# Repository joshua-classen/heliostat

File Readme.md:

Sun Follower | heliostat

This repo contains code for my heliostat robot which is able to align itself to a light source.

The heliostat in action can be viewed on youtube:

I developed and built the heliostat in year 2015
Years ago I uploaded the files to bitbucket: https://bitbucket.org/ckrex/myheliostatcontrol/src/master/

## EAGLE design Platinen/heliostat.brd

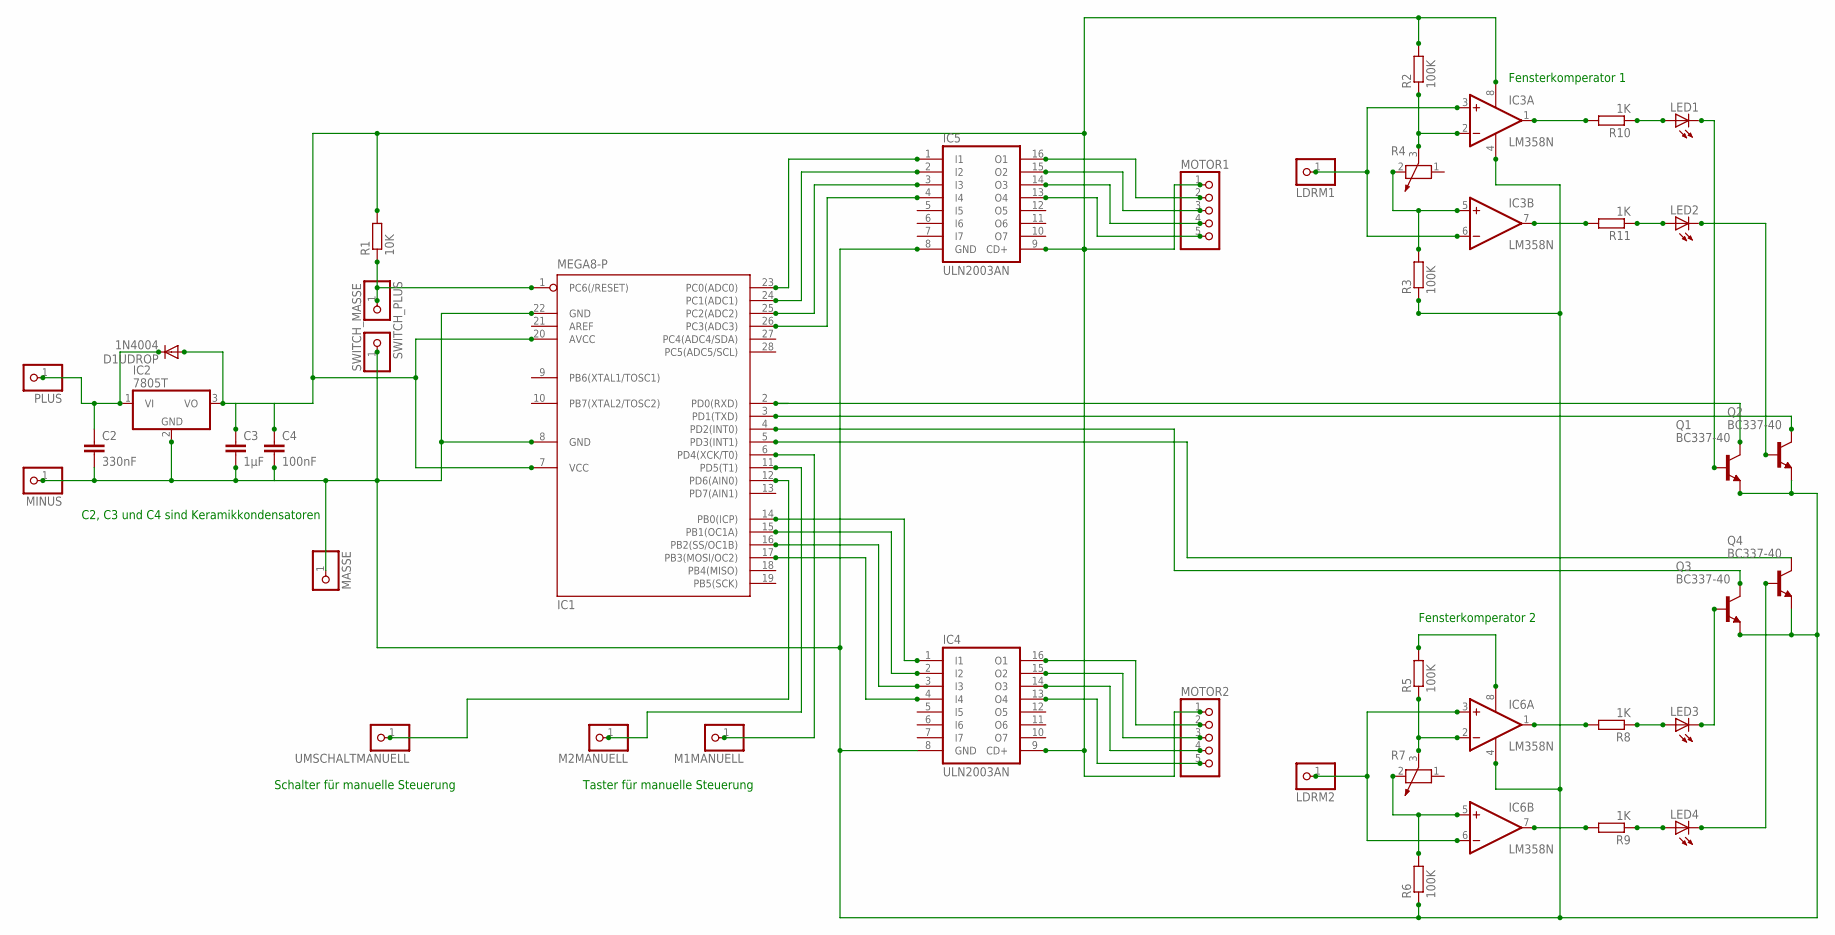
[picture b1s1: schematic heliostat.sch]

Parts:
C2: 330nF; C025-024X044
C3: 1µF; C025-024X044
C4: 100nF; C025-024X044
D1UDROP: 1N4004; DO41-10
IC1: MEGA8-P; DIL28-3
IC2: 7805T; TO220H
IC3, IC6: LM358N; DIL08
IC4, IC5: ULN2003AN; DIL16
LDRM1, LDRM2: PINHD-1X1; 1X01
LED1, LED2, LED3, LED4: LED_ELD260; LED_LD260
M1MANUELL, M2MANUELL: PINHD-1X1; 1X01
MASSE: PINHD-1X1; 1X01
MINUS: PINHD-1X1; 1X01
MOTOR1, MOTOR2: PINHD-1X5; 1X05
PLUS: PINHD-1X1; 1X01
Q1, Q2, Q3, Q4: BC337-40; TO92
R1: 10K; 0204V
R2, R3, R5, R6: 100K; 0204V
R4, R7: POTENTIOMETER_PT-10; PT-10
R8, R9, R10, R11: 1K; 0204V
SWITCH_MASSE: PINHD-1X1; 1X01
SWITCH_PLUS: PINHD-1X1; 1X01
UMSCHALTMANUELL: PINHD-1X1; 1X01

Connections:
unnamed: IC1.23 (PC0(ADC0)), IC5.1 (I1)
unnamed: IC3.2 (-IN), R2.1, R4.3
unnamed: IC1.24 (PC1(ADC1)), IC5.2 (I2)
unnamed: C2.1, D1UDROP.C, IC2.1 (VI), PLUS.1
unnamed: IC1.2 (PD0(RXD)), Q1.3 (C)
unnamed: IC1.25 (PC2(ADC2)), IC5.3 (I3)
unnamed: IC1.26 (PC3(ADC3)), IC5.4 (I4)
unnamed: IC5.16 (O1), MOTOR1.2
unnamed: IC5.15 (O2), MOTOR1.3
unnamed: IC5.14 (O3), MOTOR1.4
unnamed: IC5.13 (O4), MOTOR1.5
unnamed: IC1.14 (PB0(ICP)), IC4.1 (I1)
unnamed: IC1.15 (PB1(OC1A)), IC4.2 (I2)
unnamed: IC1.16 (PB2(SS/OC1B)), IC4.3 (I3)
unnamed: IC1.17 (PB3(MOSI/OC2)), IC4.4 (I4)
unnamed: IC4.16 (O1), MOTOR2.2
unnamed: IC4.15 (O2), MOTOR2.3
unnamed: IC4.14 (O3), MOTOR2.4
unnamed: IC4.13 (O4), MOTOR2.5
unnamed: C3.1, C4.1, D1UDROP.A, IC1.7 (VCC), IC1.20 (AVCC), IC2.3 (VO), IC3.8 (V+), IC4.9 (CD+), IC5.9 (CD+), MOTOR1.1, MOTOR2.1, R1.2, R2.2
unnamed: IC3.5 (+IN), R3.2, R4.2
unnamed: IC6.8 (V+), R5.2
unnamed: IC3.3 (+IN), IC3.6 (-IN), LDRM1.1
unnamed: IC6.1 (OUT), R8.2
unnamed: IC6.2 (-IN), R5.1, R7.3
unnamed: IC6.5 (+IN), R6.2, R7.2
unnamed: IC6.3 (+IN), IC6.6 (-IN), LDRM2.1
unnamed: LED3.A, R8.1
unnamed: IC6.7 (OUT), R9.2
unnamed: LED4.A, R9.1
unnamed: IC3.7 (OUT), R11.2
unnamed: LED2.A, R11.1
unnamed: IC3.1 (OUT), R10.2
unnamed: LED1.A, R10.1
unnamed: IC1.1 (PC6(/RESET)), R1.1, SWITCH_PLUS.1
unnamed: IC1.6 (PD4(XCK/T0)), M1MANUELL.1
unnamed: LED1.K (C), Q1.2 (B)
unnamed: LED2.K (C), Q2.2 (B)
unnamed: IC1.3 (PD1(TXD)), Q2.3 (C)
unnamed: LED3.K (C), Q3.2 (B)
unnamed: IC1.4 (PD2(INT0)), Q3.3 (C)
unnamed: LED4.K (C), Q4.2 (B)
unnamed: IC1.5 (PD3(INT1)), Q4.3 (C)
unnamed: IC1.11 (PD5(T1)), M2MANUELL.1
unnamed: C2.2, C3.2, C4.2, IC1.8 (GND), IC1.22 (GND), IC2.2 (GND), IC3.4 (V-), IC4.8 (GND), IC5.8 (GND), IC6.4 (V-), MASSE.1, MINUS.1, Q1.1 (E), Q2.1 (E), Q3.1 (E), Q4.1 (E), R3.1, R6.1, SWITCH_MASSE.1
unnamed: IC1.12 (PD6(AIN0)), UMSCHALTMANUELL.1

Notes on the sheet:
C2, C3 und C4 sind Keramikkondensatoren
Fensterkomperator 1
Fensterkomperator 2
Taster für manuelle Steuerung
Schalter für manuelle Steuerung

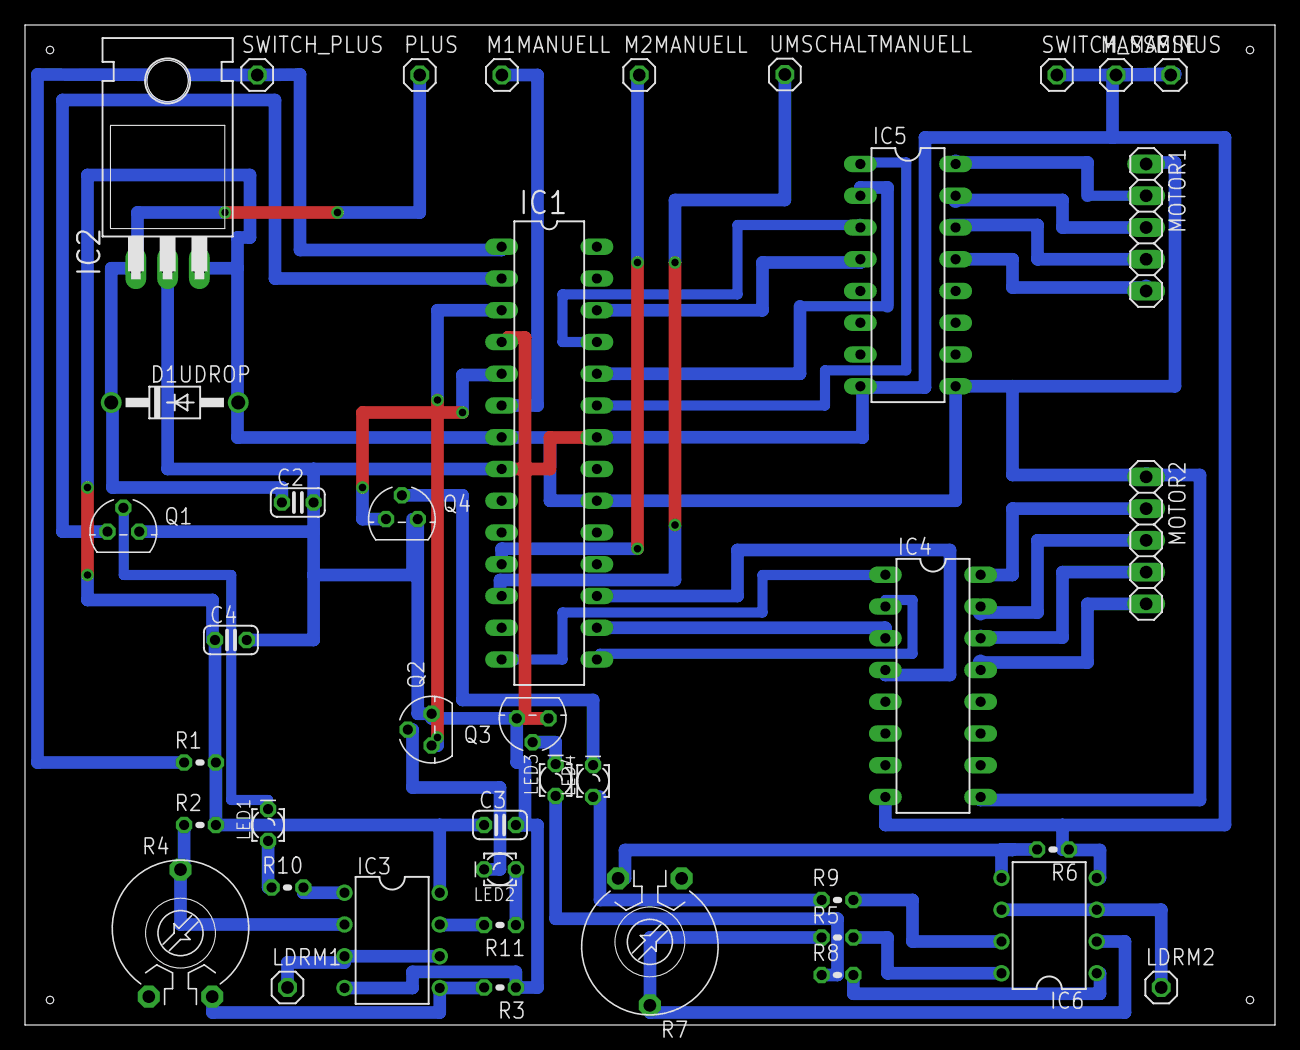
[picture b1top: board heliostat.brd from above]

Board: 2 copper layers, 100.0 x 80.0 mm, 41 parts (0 on the bottom side), 46 nets.

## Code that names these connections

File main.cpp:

/*
 * main.cpp
 *
 * Created: 10.05.2015 17:00:43
 *  Author: Joshua Classen
 */
//Die Dokumentation zu den Funktionen finden Sie in den Header (.hpp) Dateien
#define F_CPU 8000000UL       //Taktfrequenz 8MHz
//#define F_CPU 1000000UL
#include <avr/io.h>
#include <util/delay.h>

#include "motor.hpp"
#include "global.hpp"


//motor1

#define MOTOR1_PIN0  PC0
#define MOTOR1_PIN1  PC1
#define MOTOR1_PIN2  PC2
#define MOTOR1_PIN3  PC3


//motor2
#define MOTOR2_PIN0 PB0
#define MOTOR2_PIN1 PB1
#define MOTOR2_PIN2 PB2
#define MOTOR2_PIN3 PB3




#define TASTER_M1_MANUELL PD4
#define TASTER_M2_MANUELL PD5
#define TASTER_UMSCHALT_MANUELL PD6



/*

INFO:
step motor 28byj-48
Schrittmotor benötigt 2048 steps für 360°

*/
// .equ	DDRB	=$17

static bool manualcontroll = false; //manuelle Kontrolle über Taster standardmäßig nicht aktiviert.
static bool warmanualcontrollvorheraktiviert = false;




int main(void)
{
    init_atmega(); //ports initialisieren

    motor motorRollall(MOTOR1_PIN0, MOTOR1_PIN1, MOTOR1_PIN2, MOTOR1_PIN3, &PORTC);
    motor motorRollSolarpanele(MOTOR2_PIN0, MOTOR2_PIN1, MOTOR2_PIN2, MOTOR2_PIN3, &PORTB);




    while(true)
    {
		//Tasterabfrage
        if ( !(PIND & (1<<TASTER_UMSCHALT_MANUELL)) ) //wenn bit gesetz ist (pull up widerstände) // Wenn Taster gedrückt
		{
            if(warmanualcontrollvorheraktiviert == false)
            {
                manualcontroll = true;
            }
            else
            {
                manualcontroll = false;
            }
			//abfragen ob Taster vorher schon aktiviert wurde

		}

		if ( PIND & (1<<TASTER_UMSCHALT_MANUELL) ) //wenn bit nicht gesetz ist (pull up widerstände) // Wenn Taster nicht gedrückt
		{
            if(manualcontroll == true) // manualcontroll ist noch an
            {
                warmanualcontrollvorheraktiviert = true; //manualcontroll war vorher an

            }
            else //manualcontroll == false
            {
                warmanualcontrollvorheraktiviert = false;
            }
		}



		if(manualcontroll == false) //wenn manuelle Kontrolle nicht aktiviert ist, dann fürhre automatische Steuerung aus
		{

			//MOTOR1
			if ( !(PIND & (1<<PIND0)) ) //wenn bit gesetz ist (pull up widerstände)
			{
				motorRollall.rechtsrum(10,1);
			}


			if ( !(PIND & (1<<PIND1)) ) //wenn bit gesetz ist (pull up widerstände)
			{
				motorRollall.linksrum(10,1);
			}




			//MOTOR2
			if ( !(PIND & (1<<PIND2)) ) //wenn bit gesetz ist (pull up widerstände)
			{
				motorRollSolarpanele.linksrum(10,1);
			}


			if ( !(PIND & (1<<PIND3)) ) //wenn bit gesetz ist (pull up widerstände)
			{
				motorRollSolarpanele.rechtsrum(10,1);
			}

		}


		if(manualcontroll == true) //wenn manuelle Ḱontrolle aktiviert ist
		{
            if ( !(PIND & (1<<TASTER_M1_MANUELL)) ) //wenn bit gesetz ist (pull up widerstände)
            {
                motorRollall.linksrum(10,1);
            }

            if ( !(PIND & (1<<TASTER_M2_MANUELL)) ) //wenn bit gesetz ist (pull up widerstände)
            {
                motorRollSolarpanele.linksrum(10,1);
            }
		}
    }


}

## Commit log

2022-11-16 Added all code files to repo;
2022-11-17 added images, EAGLES Files and misc to repo
2022-11-17 added youtube image to Readme
